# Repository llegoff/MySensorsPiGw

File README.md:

[:fr:](LISEZMOI.md) [:uk:](README.md)

MySensorsPiGw
=============
MySensors RFM69 &amp; NRF24L Gateway for Raspberry Pi (zero &amp; B)

see
https://www.mysensors.org/build/raspberry

revision:

v1
- bad width of antenna track

v2
- change width of antenna track
- add 3.3v regulator
- add C1, C2, C3, C4

v3 
- add second NRF24L01 on SPI1
- add capacitor C5 C6
- add status leds D4 D5 D6
- change J3 position

Schema
-------

PCB
---

RFM69HW 
-------
RFM69HW is connected to SPI0

Download dev branch

    git clone https://github.com/mysensors/MySensors.git --branch development
    cd MySensors

configure (Ethernet gateway)

    ./configure --my-transport=rfm69 --my-rfm69-frequency=868 --my-is-rfm69hw --my-port=5003 --my-leds-err-pin=12 --my-leds-rx-pin=16 --my-leds-tx-pin=18
    make
    
running

    sudo ./bin/mysgw
    
install

    sudo make install
    
NRF24L01 on SPI0
----------------
Download master branch

    git clone https://github.com/mysensors/MySensors.git --branch master
    cd MySensors

configure (Ethernet gateway)

    ./configure --my-transport=nrf24 --my-rf24-irq-pin=15 --my-port=5003 --my-leds-err-pin=12 --my-leds-rx-pin=16 --my-leds-tx-pin=18
    make

running

    sudo ./bin/mysgw

install

    sudo make install

NRF24L01 on SPI1
----------------

It's experimental, see https://forum.mysensors.org/topic/7702/double-spi-radio-raspberry-pi

in /boot/config.txt add 

    //*** uncomment for pi3 ***
    //dtoverlay=pi3-disable-bt
    
    dtparam=spi=on
    //change spi1 cs0 to gpio16 pin 36
    dtoverlay=spi1-1cs,cs0_pin=16  

reboot the PI

    sudo reboot

copy the source

    cp -r MySensors MySensorsSecond
    cd MySensorsSecond

edit file `Makefile` : replace the string `mysgw` by `mysgwSecond` (in nano use Ctrl + \ )

copy file `initscripts/mysgw.systemd` and `initscripts/mysgwSecond.sysvinit` to `initscripts/mysgwSecond.systemd` and `initscripts/mysgwSecond.sysvinit` 
    
    cp initscripts/mysgw.systemd initscripts/mysgwSecond.systemd
    cp initscripts/mysgwSecond.sysvinit initscripts/mysgwSecond.sysvinit
    
edit file `initscripts/mysgwSecond.systemd` and `initscripts/mysgwSecond.sysvinit` : replace the string `mysgw` by `mysgwSecond` (in nano use Ctrl + \ ) and replace the string `MySensors Gateway` by `MySensors Gateway 2`

copy file mysgw.cpp to mysgwSecond.cpp 

    cp examples_linux/mysgw.cpp examples_linux/mysgwSecond.cpp

configure the second instance 

    ./configure --my-transport=nrf24 --my-rf24-irq-pin=33 --my-rf24-ce-pin=37 --my-rf24-cs-pin=36 --spi-spidev-device=/dev/spidev1.0 --spi-driver=SPIDEV --my-port=5004 --my-leds-err-pin=29 --my-leds-rx-pin=31 --my-leds-tx-pin=32
    make
    
running

    sudo ./bin/mysgwSecond

install

    sudo make install

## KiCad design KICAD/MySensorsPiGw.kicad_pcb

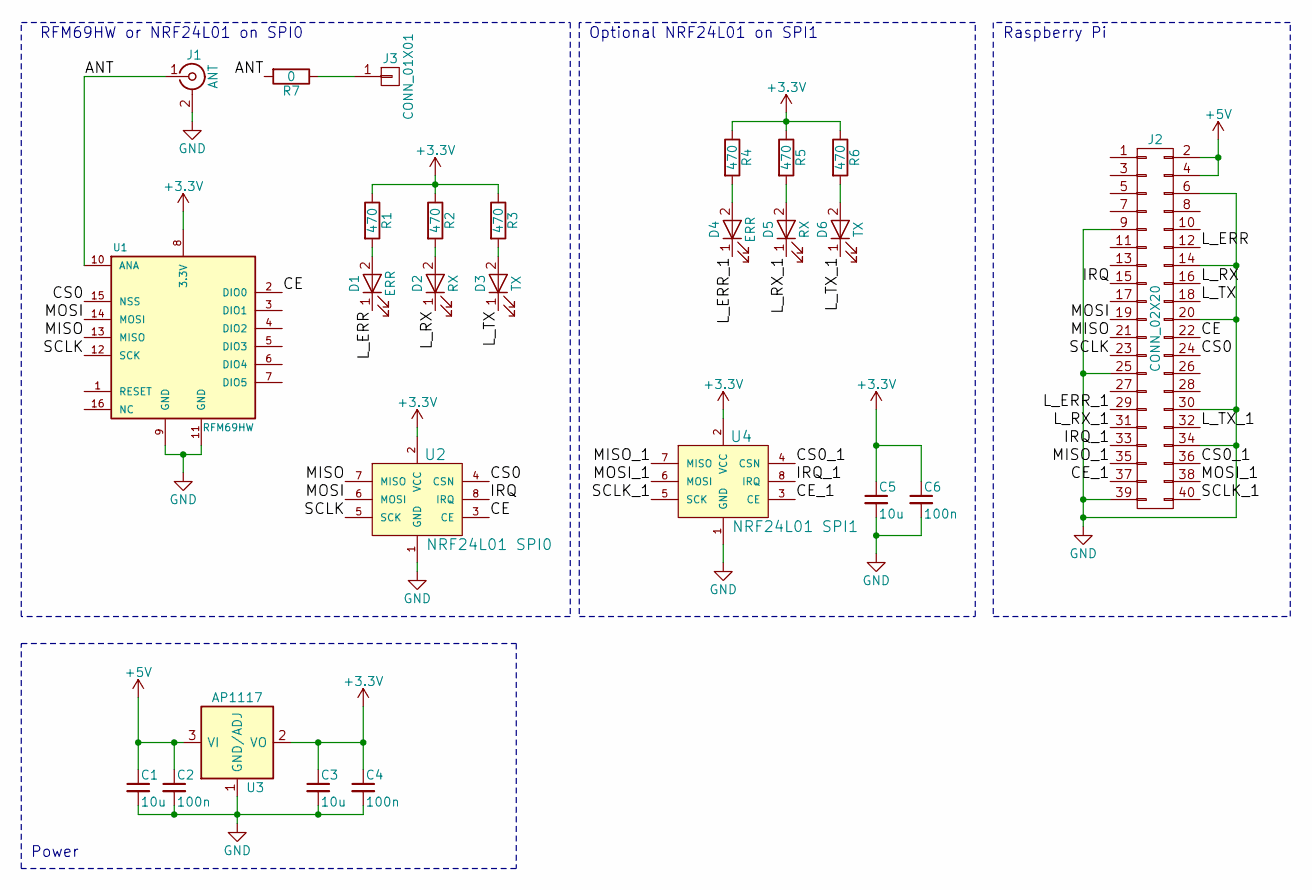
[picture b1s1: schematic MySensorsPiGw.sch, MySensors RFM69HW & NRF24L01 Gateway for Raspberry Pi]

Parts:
C1, C3, C5: 10u; C_0805
C2, C4, C6: 100n; C_0805
D1, D4: ERR; LED_0805_HandSoldering
D2, D5: RX; LED_0805_HandSoldering
D3, D6: TX; LED_0805_HandSoldering
J1: ANT; SMA_THT_Jack_Straight
J2: CONN_02X20; RaspberryPiZeroHAT
J3: CONN_01X01; PINTST
R1, R2, R3, R4, R5, R6: 470; R_0805_HandSoldering
R7: 0; R_0805_HandSoldering
U1: RFM69HW; RFM69HW_SMD_Handsoldering
U2: NRF24L01 SPI0; NRF24L01
U3: AP1117; SOT-223
U4: NRF24L01 SPI1; NRF24L01

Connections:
+3V3: C3.1, C4.1, C5.1, C6.1, R1.1, R2.1, R3.1, R4.1, R5.1, R6.1, U1.8 (3.3V), U2.2 (VCC), U3.2 (VO), U3.4 (VO), U4.2 (VCC)
+5V: C1.1, C2.1, J2.2, J2.4, U3.3 (VI)
/ANT: J1.1 (In), R7.2, U1.10 (ANA)
/CE: J2.22, U1.2 (DIO0), U2.3 (CE)
/CE_1: J2.37, U4.3 (CE)
/CS0: J2.24, U1.15 (NSS), U2.4 (CSN)
/CS0_1: J2.36, U4.4 (CSN)
/IRQ: J2.15, U2.8 (IRQ)
/IRQ_1: J2.33, U4.8 (IRQ)
/L_ERR: D1.1 (K), J2.12
/L_ERR_1: D4.1 (K), J2.29
/L_RX: D2.1 (K), J2.16
/L_RX_1: D5.1 (K), J2.31
/L_TX: D3.1 (K), J2.18
/L_TX_1: D6.1 (K), J2.32
/MISO: J2.21, U1.13 (MISO), U2.7 (MISO)
/MISO_1: J2.35, U4.7 (MISO)
/MOSI: J2.19, U1.14 (MOSI), U2.6 (MOSI)
/MOSI_1: J2.38, U4.6 (MOSI)
/SCLK: J2.23, U1.12 (SCK), U2.5 (SCK)
/SCLK_1: J2.40, U4.5 (SCK)
GND: C1.2, C2.2, C3.2, C4.2, C5.2, C6.2, J1.2 (Ext), J2.6, J2.9, J2.14, J2.20, J2.25, J2.30, J2.34, J2.39, U1.9 (GND), U1.11 (GND), U2.1 (GND), U3.1 (GND/ADJ), U4.1 (GND)
unnamed: D1.2 (A), R1.2
unnamed: D2.2 (A), R2.2
unnamed: D3.2 (A), R3.2
unnamed: D4.2 (A), R4.2
unnamed: D5.2 (A), R5.2
unnamed: D6.2 (A), R6.2
unnamed: J3.1, R7.1

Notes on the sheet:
Optional NRF24L01 on SPI1
RFM69HW or NRF24L01 on SPI0
Raspberry Pi
Power

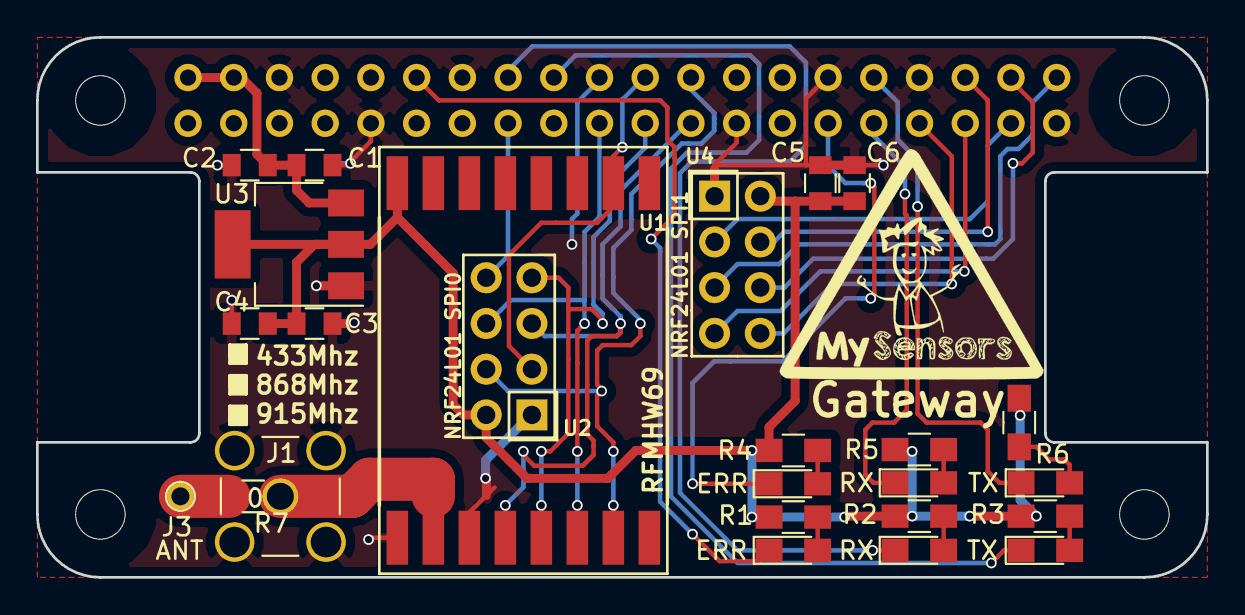
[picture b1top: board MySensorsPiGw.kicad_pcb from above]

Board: 2 copper layers, 65.0 x 30.0 mm, 26 parts (0 on the bottom side), 29 nets.

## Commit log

2017-08-30 readme
2017-08-31 impedence
2017-08-31 v2img
2017-08-31 v2gerber
2017-08-31 v2kicad
2017-08-31 v2bom
2017-09-14 updatev2
2017-10-04 v3 Gerber
2017-10-04 v3 kicad
2017-10-04 v3 img
2018-04-26 Fix instructions
    `-d` flag not anymore available on MySensors --development branch.
    Fix #1
2018-04-26 Add "reboot" hint
    Fixes #3
